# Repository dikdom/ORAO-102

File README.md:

# ORAO 102
This repository contains enhancements for the 2007 rebuild of the Yugoslavian ORAO-102 computer.

The source of all materials are here: http://www.deltasoft.com.hr/projects/orao2007.php?title=Orao%202007

Also a lot of materials can be found here: https://github.com/mejs/orao

Updated keyboard gerber with fixed (!) matrix can be found here: https://github.com/tothrick/orao-keyboard
According to Rick the IC13 should be LS instead of HC because HC chips produces errors on keyboard input..

I created rev2 orao motherboard because all the silk text was completely misaligned and I heard about the missing lines also in
the video circuitry.

The rev2 and rev3 materials both contains the 'missing lines' fix. Rev3 also contains fix for the pull-up of the 
pin36 (BE line) of the WDC 65C02 CPU. In case of using a 65C02 CPU then R1 should be populated. If the
CPU is an NMOS 6502 (MOS, Rockwell) the pull-up doesn't interfere with the operation. 

I created rev3 because I still messed up the texts on rev2 board, the pull-up is inserted and the R5 value is corrected.
I added an extra pinheader line for the keyboard. I had to move everything from EagleCAD to KiCad. I'm not a big
expert on that, so... 

The clock (IC14) and the pixel shift IC (IC8) must be 7404/74165 (or LS), the rest can be HC. You may use 74LS for the complete board. 

On the ORAO2007 the keyboard connection header is a simple DIP16 socket. I added a second line of 1x8 header, so
a 2x8 pin header (socket) also can be populated there - if that is more convenient. (for a keyboard PCB please
check the links above).

I build the rev2 board for myself. I used a 7404 for IC14 and a 74LS165 for IC8. The remaining 74 logic ICs are 74HC
class ICs.

rev3 board is not manufactured/tried yet so... be the first one, and go where noone ever gone before... (but let me know the result!)

## Troubleshooting
First check if the 74LS04 (or 7404) generates the 8MHz clock. I found a few conterfeit 74LS04 ICs that didn't work. 
Don't even bother with 74HC04 or 74HCT04 chips, they won't work here.

In case clock is present but screen is black, check the 1MHz output of IC22 (pin 6). If there is 8MHz input but no output
then IC22 shall be replaced...

Rev3 has tinted vias but please check your solderings. 

In case you have a prompt on the screen but it is garbled then probably R5 is still too high for you. It was set to
1k on the original (ORAO 2007) plan, but for me that had to be lowered to 700R (another one to 750R). 620R should be
fine for everyone, but who knows.

Good luck!

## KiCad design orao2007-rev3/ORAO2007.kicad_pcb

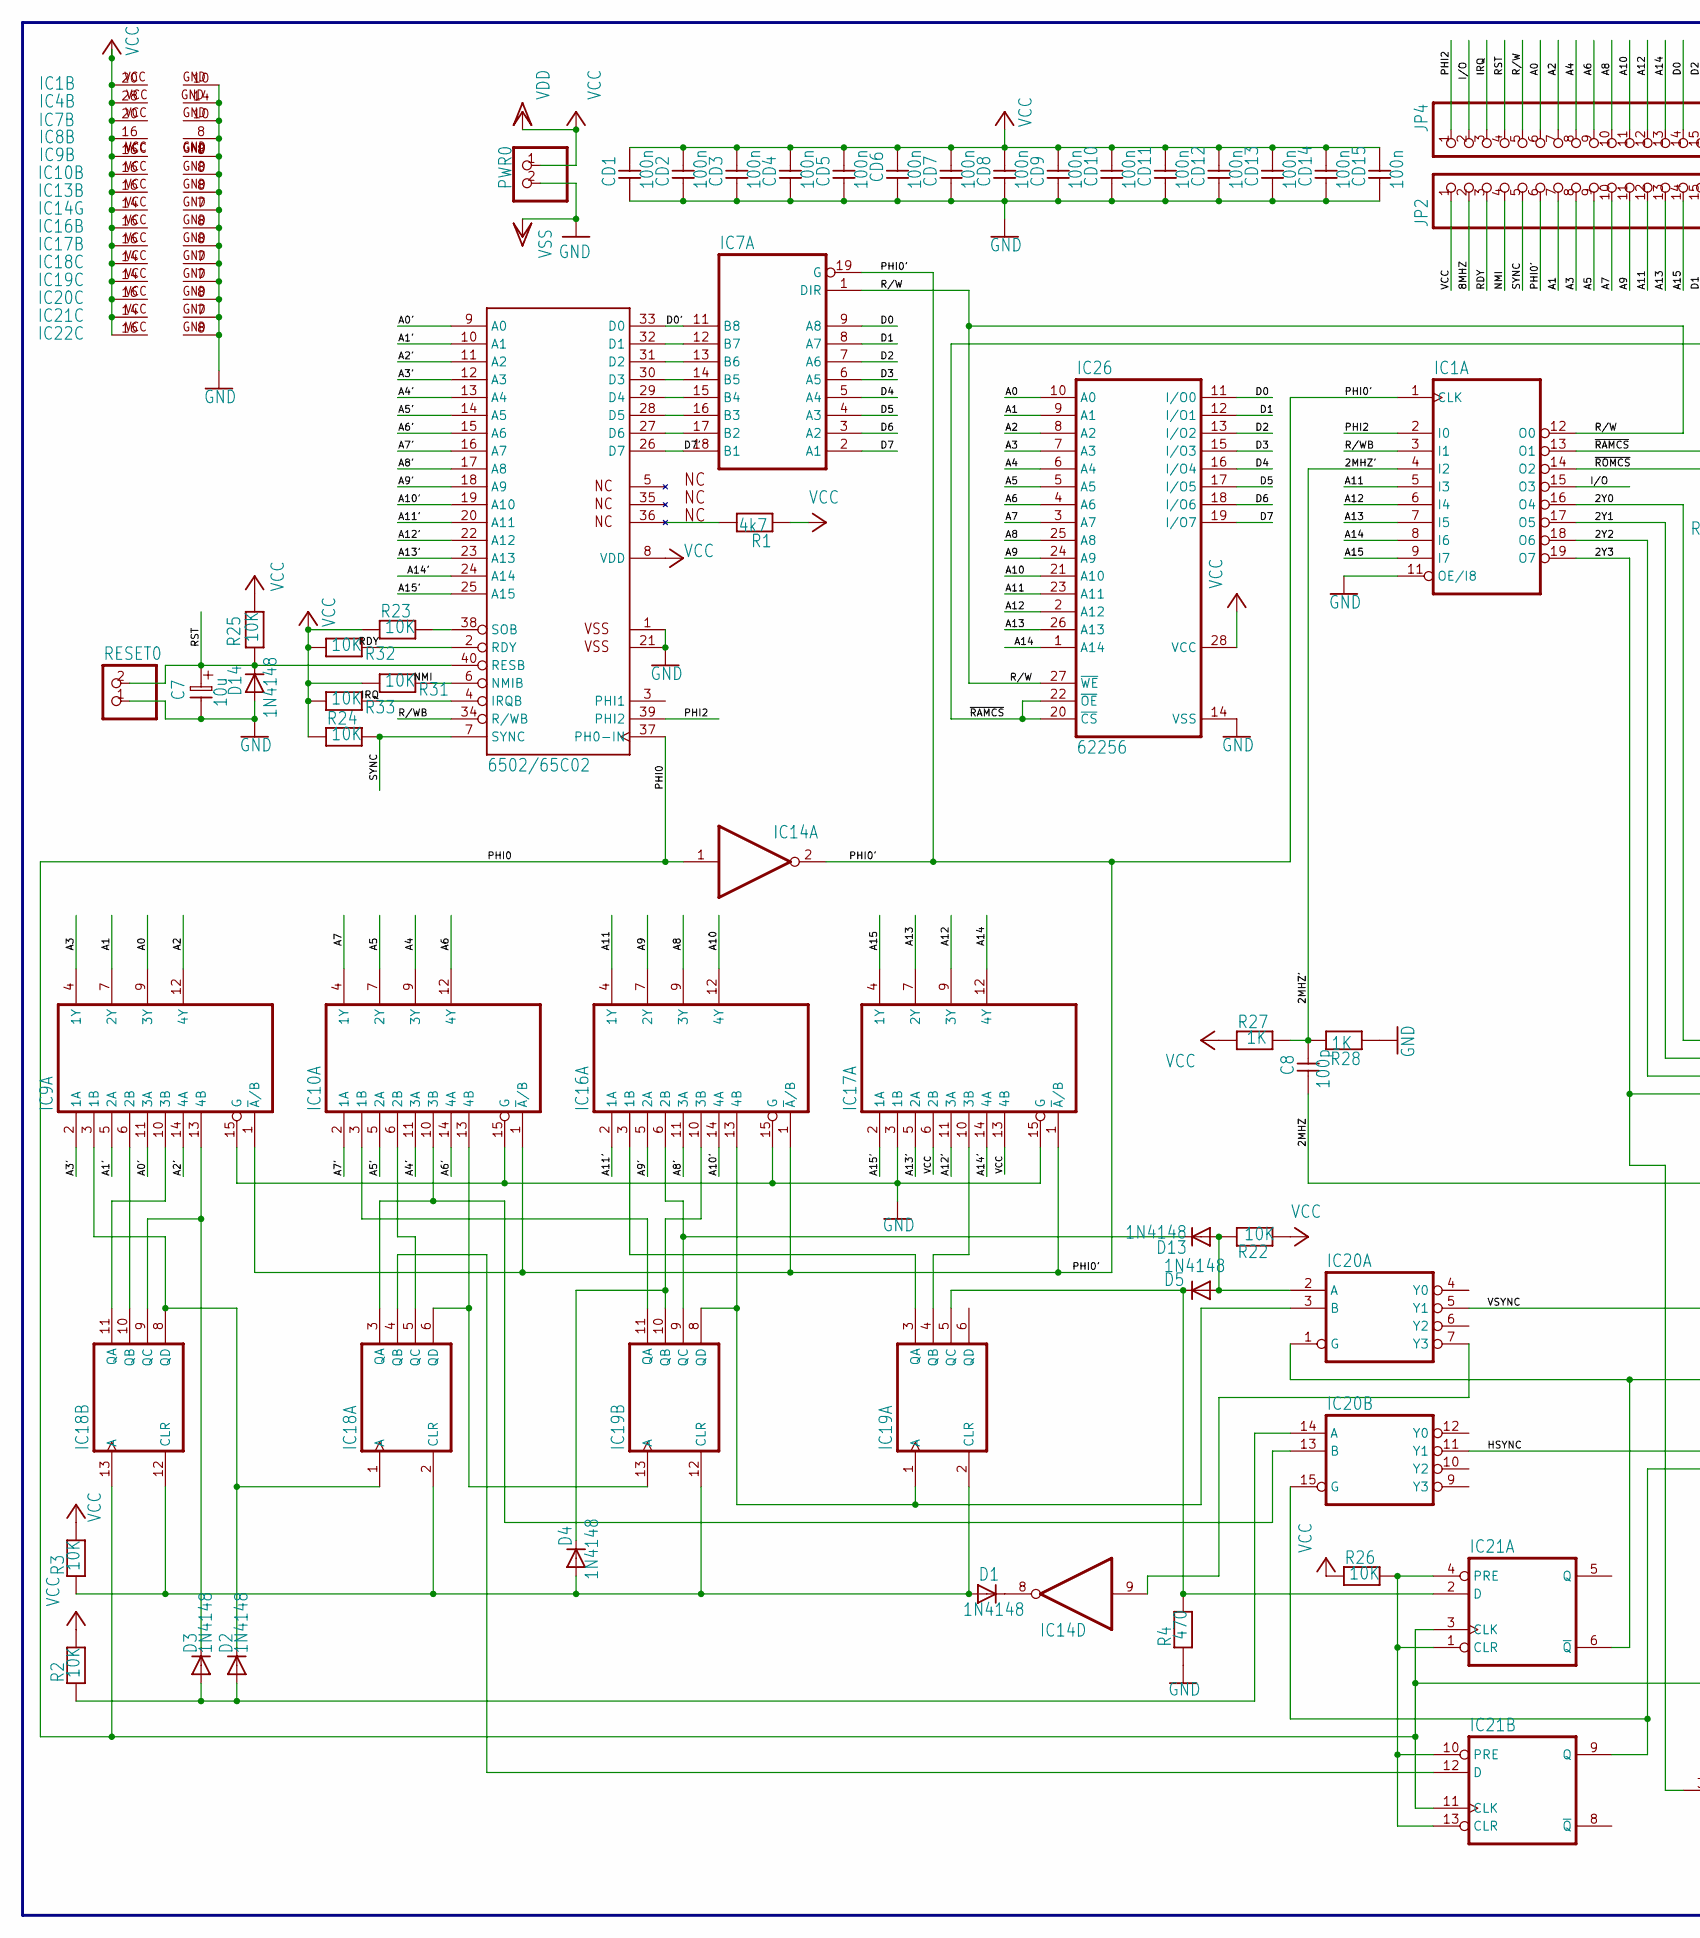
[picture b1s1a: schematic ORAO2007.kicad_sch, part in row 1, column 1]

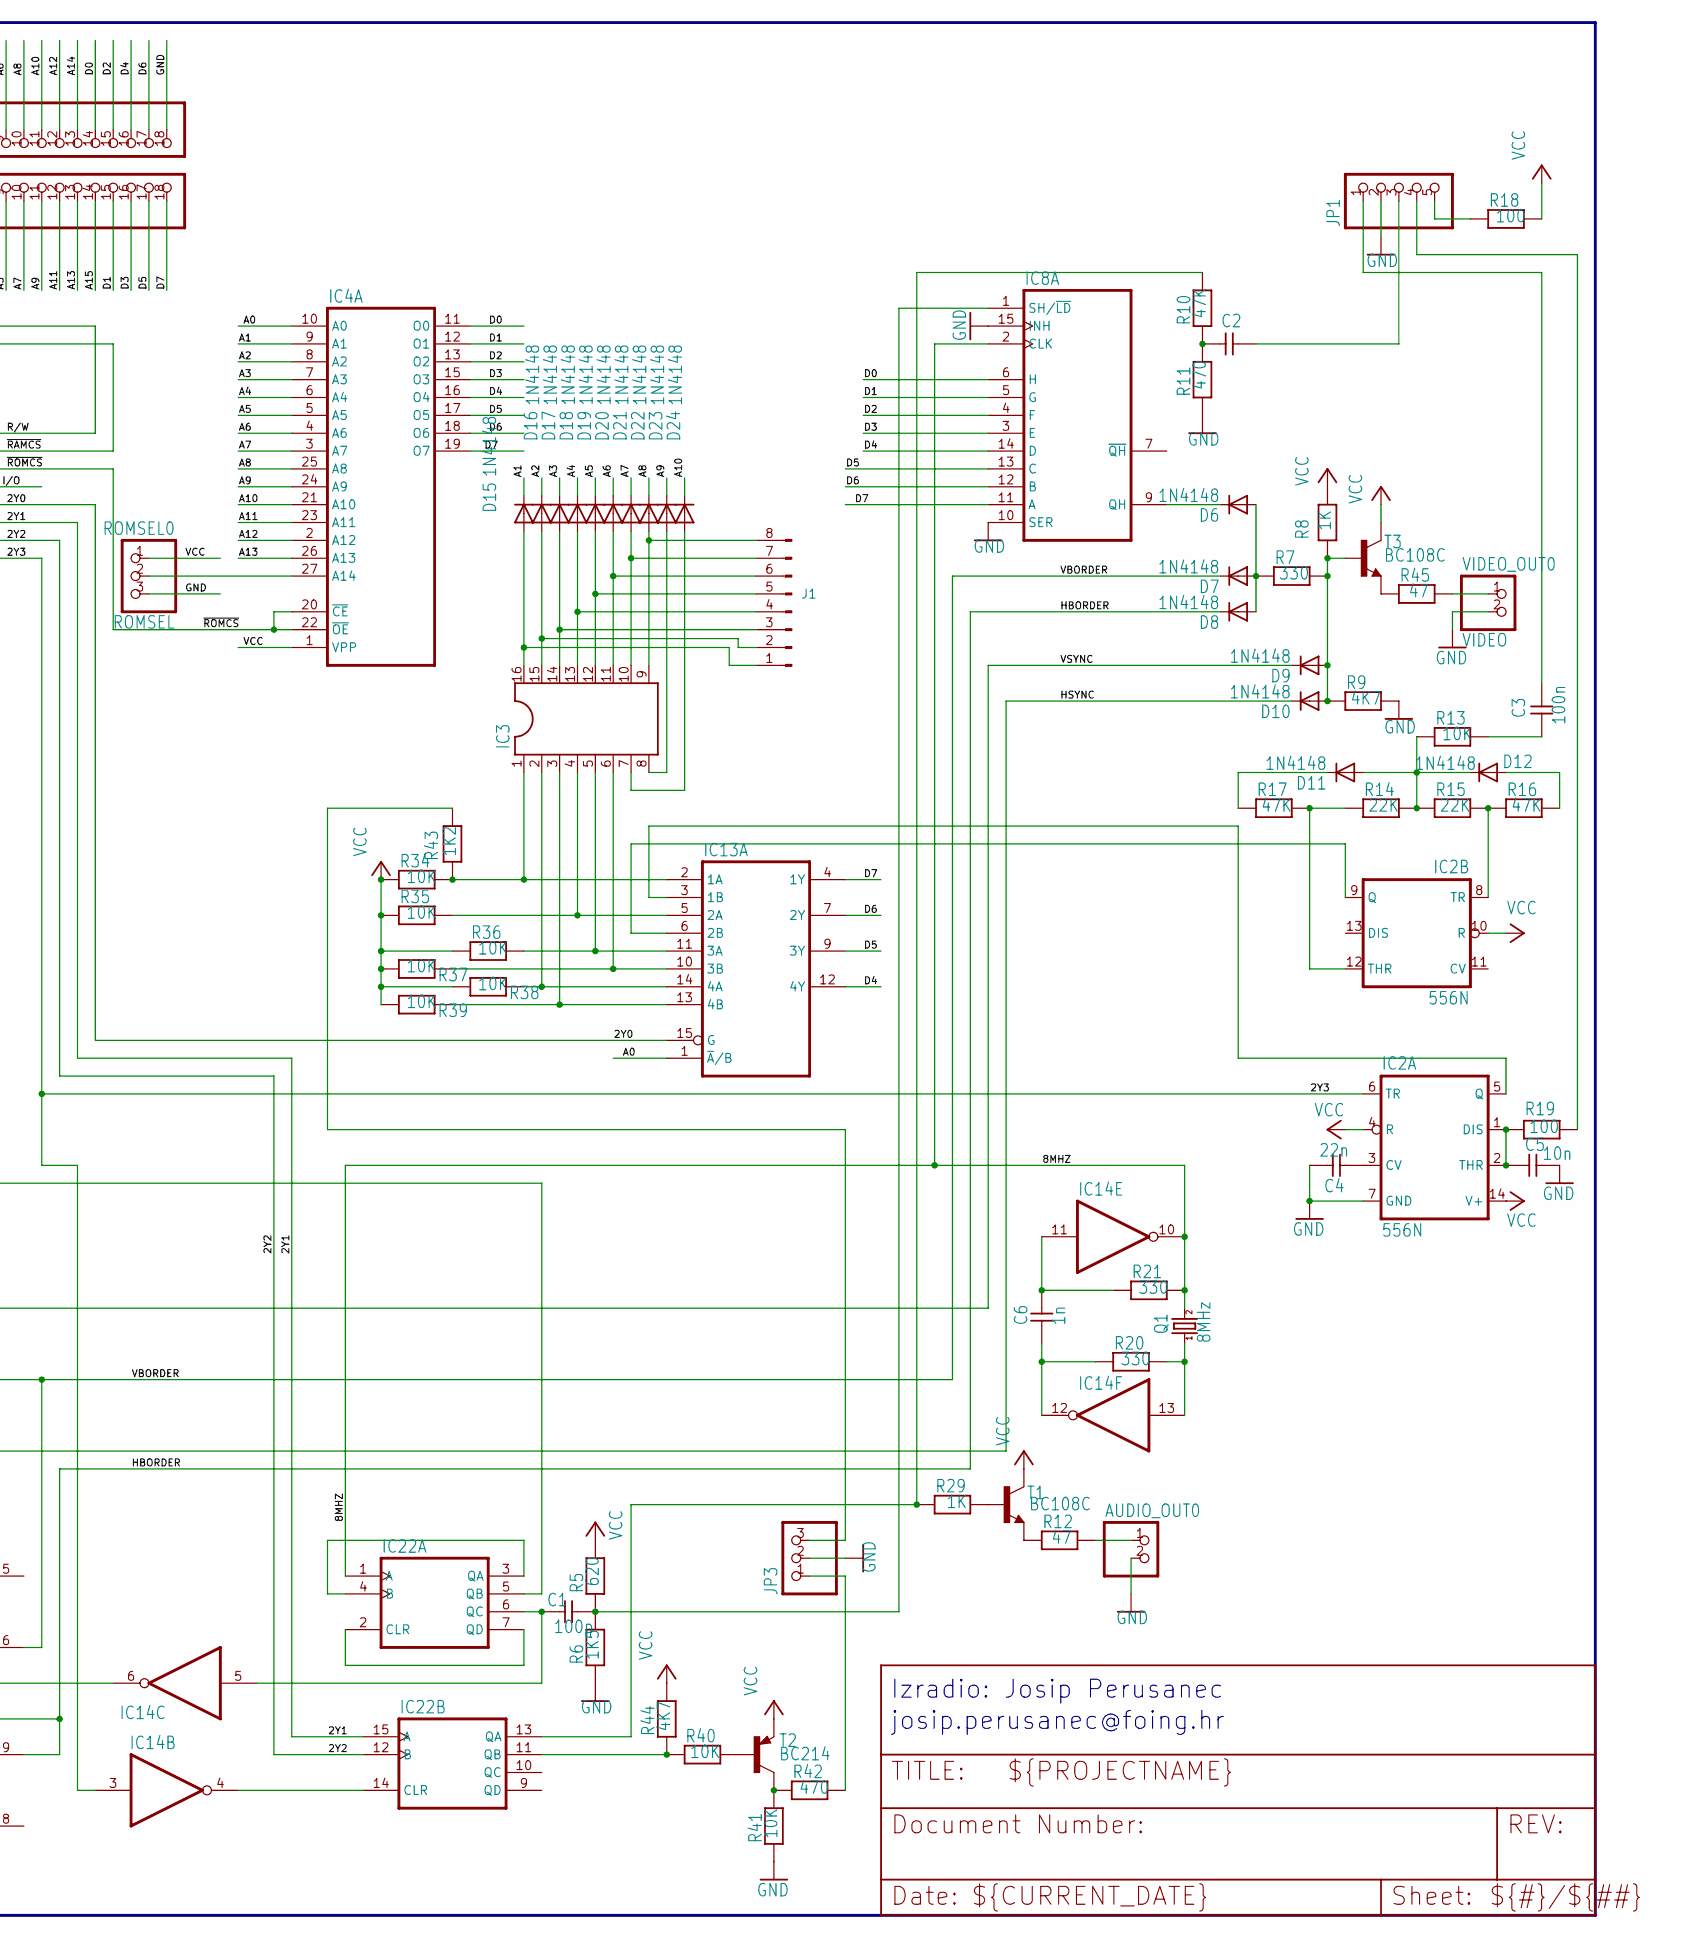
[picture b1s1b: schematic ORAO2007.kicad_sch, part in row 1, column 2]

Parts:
AUDIO_OUT0: PINHD-1X2; 1X02
C1, C8: 100p; C-5
C2: CAPNP-5; C-5
C3: 100n; C-5
C4: 22n; C-5
C5: 10n; C-5
C6: 1n; C-5
C7: 10u; ES-2,5L
CD1, CD2, CD3, CD4, CD5, CD6, CD7, CD8, CD9, CD10, CD11, CD12, CD13, CD14, CD15: 100n; C-5
D1, D2, D3, D4, D5, D6, D7, D8, D9, D10, D11, D12, D13, D14, D15, D16, D17, D18, D19, D20, D21, D22, D23, D24: 1N4148; DO35-10
IC1: GAL16V8; DIL20
IC2: 556N; DIL14
IC3: DIL16S; SOCKED-16
IC4: 27256; DIL28
IC7: 74245N; DIL20
IC8: 74165N; DIL16
IC9, IC10, IC13, IC16, IC17: 74257N; DIL16
IC14: 7404N; DIL14
IC18, IC19: 74393N; DIL14
IC20: 74139N; DIL16
IC21: 7474N; DIL14
IC22: 74390N; DIL16
IC26: 62256; DIL28-6
J1: Conn_01x08_Pin; PinHeader_1x08_P2.54mm_Vertical
JP1: PINHD-1X5; 1X05
JP2, JP4: PINHD-1X18; 1X18
JP3: PINHD-1X3; 1X03
PWR0: PINHD-1X2; 1X02
Q1: 8MHz; HC49_S
R1: 4k7; R-7,5
R2, R3, R13, R22, R23, R24, R25, R26, R31, R32, R33, R34, R35, R36, R37, R38, R39, R40, R41: 10K; R-7,5
R4, R11, R42: 470; R-7,5
R5: 620; R-7,5
R6: 1K5; R-7,5
R7, R20, R21: 330; R-7,5
R8, R27, R28, R29: 1K; R-7,5
R9, R44: 4K7; R-7,5
R10, R16, R17: 47K; R-7,5
R12, R45: 47; R-7,5
R14, R15: 22K; R-7,5
R18, R19: 100; R-7,5
R43: 1K2; R-7,5
RESET0: PINHD-1X2; 1X02
ROMSEL0: ROMSEL; 1X03
T1, T3: BC108C; TO18
T2: BC214; TO92
U2: 6502/65C02; DIP-40
VIDEO_OUT0: VIDEO; 1X02

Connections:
/2MHZ: C8.2, IC22.5 (QB)
/2MHZ': C8.1, IC1.4 (I2), R27.1, R28.2
/2Y0: IC1.16 (O4), IC13.15 (G)
/2Y1: IC1.17 (O5), IC22.15 (A)
/2Y2: IC1.18 (O6), IC22.12 (B)
/2Y3: IC1.19 (O7), IC2.6 (TR), IC14.3 (I)
/8MHZ: IC8.2 (CLK), IC14.10 (O), IC22.1 (A), JP2.2, Q1.2, R21.2
/A0: IC4.10 (A0), IC9.9 (3Y), IC13.1 (~A/B), IC26.10 (A0), JP4.6
/A0': IC9.11 (3A), U2.9 (A0)
/A1: D15.C, IC4.9 (A1), IC9.7 (2Y), IC26.9 (A1), JP2.7
/A1': IC9.5 (2A), U2.10 (A1)
/A2: D16.C, IC4.8 (A2), IC9.12 (4Y), IC26.8 (A2), JP4.7
/A2': IC9.14 (4A), U2.11 (A2)
/A3: D17.C, IC4.7 (A3), IC9.4 (1Y), IC26.7 (A3), JP2.8
/A3': IC9.2 (1A), U2.12 (A3)
/A4: D18.C, IC4.6 (A4), IC10.9 (3Y), IC26.6 (A4), JP4.8
/A4': IC10.11 (3A), U2.13 (A4)
/A5: D19.C, IC4.5 (A5), IC10.7 (2Y), IC26.5 (A5), JP2.9
/A5': IC10.5 (2A), U2.14 (A5)
/A6: D20.C, IC4.4 (A6), IC10.12 (4Y), IC26.4 (A6), JP4.9
/A6': IC10.14 (4A), U2.15 (A6)
/A7: D21.C, IC4.3 (A7), IC10.4 (1Y), IC26.3 (A7), JP2.10
/A7': IC10.2 (1A), U2.16 (A7)
/A8: D22.C, IC4.25 (A8), IC16.9 (3Y), IC26.25 (A8), JP4.10
/A8': IC16.11 (3A), U2.17 (A8)
/A9: D23.C, IC4.24 (A9), IC16.7 (2Y), IC26.24 (A9), JP2.11
/A9': IC16.5 (2A), U2.18 (A9)
/A10: D24.C, IC4.21 (A10), IC16.12 (4Y), IC26.21 (A10), JP4.11
/A10': IC16.14 (4A), U2.19 (A10)
/A11: IC1.5 (I3), IC4.23 (A11), IC16.4 (1Y), IC26.23 (A11), JP2.12
/A11': IC16.2 (1A), U2.20 (A11)
/A12: IC1.6 (I4), IC4.2 (A12), IC17.9 (3Y), IC26.2 (A12), JP4.12
/A12': IC17.11 (3A), U2.22 (A12)
/A13: IC1.7 (I5), IC4.26 (A13), IC17.7 (2Y), IC26.26 (A13), JP2.13
/A13': IC17.5 (2A), U2.23 (A13)
/A14: IC1.8 (I6), IC17.12 (4Y), IC26.1 (A14), JP4.13
/A14': IC17.14 (4A), U2.24 (A14)
/A15: IC1.9 (I7), IC17.4 (1Y), JP2.14
/A15': IC17.2 (1A), U2.25 (A15)
/D0: IC4.11 (O0), IC7.9 (A8), IC8.6 (H), IC26.11 (I/O0), JP4.14
/D0': IC7.11 (B8), U2.33 (D0)
/D1: IC4.12 (O1), IC7.8 (A7), IC8.5 (G), IC26.12 (I/O1), JP2.15
/D2: IC4.13 (O2), IC7.7 (A6), IC8.4 (F), IC26.13 (I/O2), JP4.15
/D3: IC4.15 (O3), IC7.6 (A5), IC8.3 (E), IC26.15 (I/O3), JP2.16
/D4: IC4.16 (O4), IC7.5 (A4), IC8.14 (D), IC13.12 (4Y), IC26.16 (I/O4), JP4.16
/D5: IC4.17 (O5), IC7.4 (A3), IC8.13 (C), IC13.9 (3Y), IC26.17 (I/O5), JP2.17
/D6: IC4.18 (O6), IC7.3 (A2), IC8.12 (B), IC13.7 (2Y), IC26.18 (I/O6), JP4.17
/D7: IC4.19 (O7), IC7.2 (A1), IC8.11 (A), IC13.4 (1Y), IC26.19 (I/O7), JP2.18
/D7': IC7.18 (B1), U2.26 (D7)
/HBORDER: D8.C, IC20.15 (G), IC21.9 (Q)
/HSYNC: D10.C, IC20.11 (Y1)
/IRQ: JP4.3, R33.2, U2.4 (IRQB)
/I/O: IC1.15 (O3), JP4.2
/NMI: JP2.4, R31.2, U2.6 (NMIB)
/PHI0: IC14.1 (I), IC14.6 (O), IC18.13 (A), IC21.3 (CLK), IC21.11 (CLK), U2.37 (PH0-IN)
/PHI0': IC1.1 (CLK), IC7.19 (G), IC9.1 (~A/B), IC10.1 (~A/B), IC14.2 (O), IC16.1 (~A/B), IC17.1 (~A/B), JP2.6
/PHI2: IC1.2 (I0), JP4.1, U2.39 (PHI2)
/RDY: JP2.3, R32.2, U2.2 (RDY)
/RST: C7.1, D14.C, JP4.4, R25.1, RESET0.2, U2.40 (RESB); also elsewhere on the board
/R/W: IC1.12 (O0), IC7.1 (DIR), IC26.27 (~WE), JP4.5
/R/WB: IC1.3 (I1), U2.34 (R/WB)
/SYNC: JP2.5, R24.2, U2.7 (SYNC)
/VBORDER: D7.C, IC20.1 (G), IC21.6 (~Q)
/VSYNC: D9.C, IC20.5 (Y1)
/~RAMCS: IC1.13 (O1), IC26.20 (~CS), IC26.22 (~OE)
/~ROMCS: IC1.14 (O2), IC4.20 (~CE), IC4.22 (~OE)
GND: AUDIO_OUT0.2, C4.2, C5.2, C7.2, CD1.1, CD2.1, CD3.1, CD4.1, CD5.1, CD6.1, CD7.1, CD8.1, CD9.1, CD10.1, CD11.1, CD12.1, CD13.1, CD14.1, CD15.1, D14.A, IC1.10 (GND), IC1.11 (OE/I8), IC2.7 (GND), IC4.14 (GND), IC7.10 (GND), IC8.8 (GND), IC8.10 (SER), IC8.15 (INH), IC9.8 (GND), IC9.15 (G), IC10.8 (GND), IC10.15 (G), IC13.8 (GND), IC14.7 (GND), IC16.8 (GND), IC16.15 (G), IC17.3 (1B), IC17.8 (GND), IC17.15 (G), IC18.7 (GND), IC19.7 (GND), IC20.8 (GND), IC21.7 (GND), IC22.8 (GND), IC26.14 (VSS), JP1.2, JP3.2, JP4.18, PWR0.2, R4.1, R6.1, R9.2, R11.1, R28.1, R41.2, RESET0.1, ROMSEL0.3, U2.1 (VSS$1), U2.21 (VSS$2), VIDEO_OUT0.2; also elsewhere on the board
unnamed 67: AUDIO_OUT0.1, R12.2; also elsewhere on the board
unnamed: C2.1, JP1.3
unnamed: C2.2, R10.2, R11.2
unnamed: C3.1, R13.1
unnamed: C3.2, JP1.1
unnamed: D6.A, D7.A, D8.A, R7.1
unnamed: D11.A, D12.C, R13.2, R14.2, R15.1
unnamed: D11.C, R17.1
unnamed: D12.A, R16.2
unnamed: D23.A, IC3.8
unnamed: D24.A, IC3.7
unnamed: C4.1, IC2.3 (CV)
unnamed: C5.1, IC2.1 (DIS), IC2.2 (THR), R19.1
unnamed: IC2.12 (THR), R14.1, R17.2
unnamed: IC2.8 (TR), R15.2, R16.1
unnamed: IC4.27 (A14), ROMSEL0.2
unnamed: IC7.17 (B2), U2.27 (D6)
unnamed: IC7.16 (B3), U2.28 (D5)
unnamed: IC7.15 (B4), U2.29 (D4)
unnamed: IC7.14 (B5), U2.30 (D3)
unnamed: IC7.13 (B6), U2.31 (D2)
unnamed: IC7.12 (B7), U2.32 (D1)
unnamed: D6.C, IC8.9 (QH)
unnamed: C1.2, IC8.1 (SH/~LD), R5.1, R6.2
unnamed: IC10.3 (1B), IC19.11 (QA)
unnamed: IC10.6 (2B), IC18.5 (QC)
unnamed: IC10.10 (3B), IC18.3 (QA), IC20.13 (B)
unnamed: IC10.13 (4B), IC18.6 (QD), IC19.13 (A)
unnamed: IC3.1, IC13.2 (1A), R34.2, R43.1
unnamed: IC2.5 (Q), IC13.3 (1B)
unnamed: IC3.4, IC13.5 (2A), R35.2
unnamed: IC2.9 (Q), IC13.6 (2B)
unnamed: IC3.5, IC13.11 (3A), R36.2
unnamed: IC3.6, IC13.10 (3B), R37.2
unnamed: IC3.2, IC13.14 (4A), R38.2
unnamed: IC3.3, IC13.13 (4B), R39.2
unnamed: IC14.4 (O), IC22.14 (CLR)
unnamed: C1.1, IC14.5 (I), IC22.6 (QC)
unnamed: IC14.9 (I), IC20.7 (Y3)
unnamed: D1.C, IC14.8 (O)
unnamed: C6.2, IC14.11 (I), R21.1
unnamed: IC14.13 (I), Q1.1, R20.2
unnamed: C6.1, IC14.12 (O), R20.1
unnamed: IC16.3 (1B), IC19.3 (QA)
unnamed: D13.C, IC16.6 (2B), IC19.9 (QC)
unnamed: D4.C, IC16.10 (3B), IC19.10 (QB)
unnamed: IC16.13 (4B), IC19.1 (A), IC19.8 (QD), IC20.3 (B)
unnamed: IC17.10 (3B), IC19.4 (QB)
unnamed: D2.C, IC9.3 (1B), IC18.1 (A), IC18.8 (QD)
unnamed: D1.A, D4.A, IC18.2 (CLR), IC18.12 (CLR), IC19.2 (CLR), IC19.12 (CLR), R3.2
unnamed: IC18.4 (QB), IC21.12 (D)
unnamed: IC9.10 (3B), IC18.11 (QA)
unnamed: IC9.6 (2B), IC18.10 (QB)
unnamed: D3.C, IC9.13 (4B), IC18.9 (QC)
unnamed: D5.C, IC19.5 (QC), IC21.2 (D), R4.2
unnamed: D5.A, D13.A, IC20.2 (A), R22.1
unnamed: D2.A, D3.A, IC20.14 (A), R2.2
unnamed: IC21.1 (CLR), IC21.4 (PRE), IC21.10 (PRE), IC21.13 (CLR), R26.2
unnamed: IC22.3 (QA), IC22.4 (B)
unnamed: IC22.2 (CLR), IC22.7 (QD)
unnamed: IC22.13 (QA), R10.1, R29.2
unnamed: IC22.11 (QB), R40.1, R44.1
unnamed: D15.A, IC3.16, J1.1
unnamed: D16.A, IC3.15, J1.2
unnamed: D17.A, IC3.14, J1.3
unnamed: D18.A, IC3.13, J1.4
unnamed: D19.A, IC3.12, J1.5
unnamed: D20.A, IC3.11, J1.6
unnamed: D21.A, IC3.10, J1.7
unnamed: D22.A, IC3.9, J1.8
unnamed: JP1.4, R19.2
unnamed: JP1.5, R18.2
unnamed: JP3.1, R42.1
unnamed: JP3.3, R43.2
unnamed 141: R45.2, VIDEO_OUT0.1; also elsewhere on the board
unnamed: R29.1, T1.2 (B)
unnamed: R12.1, T1.1 (E)
unnamed: R40.2, T2.2 (B)
unnamed: R41.1, R42.2, T2.3 (C)
unnamed: D9.A, D10.A, R7.2, R8.1, R9.1, T3.2 (B)
unnamed: R45.1, T3.1 (E)
unnamed: R23.2, U2.38 (SOB)
VCC: CD1.2, CD2.2, CD3.2, CD4.2, CD5.2, CD6.2, CD7.2, CD8.2, CD9.2, CD10.2, CD11.2, CD12.2, CD13.2, CD14.2, CD15.2, IC1.20 (VCC), IC2.4 (R), IC2.10 (R), IC2.14 (V+), IC4.1 (VPP), IC4.28 (VCC), IC7.20 (VCC), IC8.16 (VCC), IC9.16 (VCC), IC10.16 (VCC), IC13.16 (VCC), IC14.14 (VCC), IC16.16 (VCC), IC17.6 (2B), IC17.13 (4B), IC17.16 (VCC), IC18.14 (VCC), IC19.14 (VCC), IC20.16 (VCC), IC21.14 (VCC), IC22.16 (VCC), IC26.28 (VCC), JP2.1, PWR0.1, R1.1, R2.1, R3.1, R5.2, R8.2, R18.1, R22.2, R23.1, R24.1, R25.2, R26.1, R27.2, R31.1, R32.1, R33.1, R34.1, R35.1, R36.1, R37.1, R38.1, R39.1, R44.2, ROMSEL0.1, T1.3 (C), T2.1 (E), T3.3 (C), U2.8 (VDD); also elsewhere on the board

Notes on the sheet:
josip.perusanec@foing.hr
Izradio: Josip Perusanec

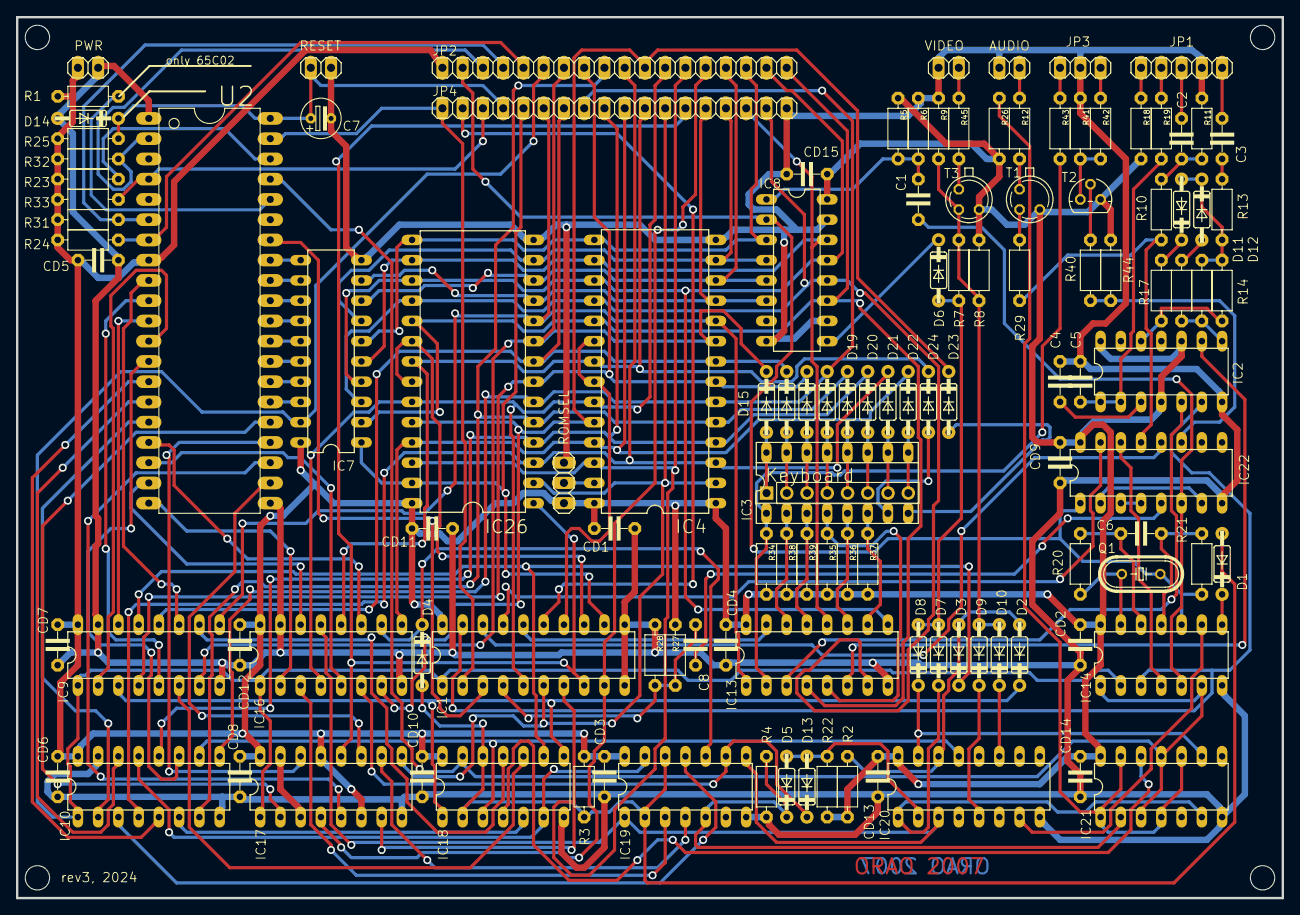
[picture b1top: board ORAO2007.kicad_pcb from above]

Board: 16 copper layers, 158.8 x 110.5 mm, 128 parts (0 on the bottom side), 150 nets.

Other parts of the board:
@HOLE0, @HOLE1, @HOLE2, @HOLE3: (no value)
AUDIO: PINHD-1X2; 1X02
PWR: PINHD-1X2; 1X02
RESET: PINHD-1X2; 1X02
VIDEO: VIDEO; 1X02

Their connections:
/RST: RESET.2; also elsewhere on the board
GND: AUDIO.2, PWR.2, RESET.1, VIDEO.2; also elsewhere on the board
unnamed 67: AUDIO.1; also elsewhere on the board
unnamed 141: VIDEO.1; also elsewhere on the board
VCC: PWR.1; also elsewhere on the board

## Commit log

2024-05-17 Update README.md
    Keyboard gerber link
2025-07-07 ROM dissassembly, MCU binary firmware
2025-07-07 Create README.md
    Description of the ROM dissassembly
2025-07-07 Create README.md for cart firmware
2025-07-08 Update README.md
    comm "?" is also serbo-croatian, +1 typo fixed
